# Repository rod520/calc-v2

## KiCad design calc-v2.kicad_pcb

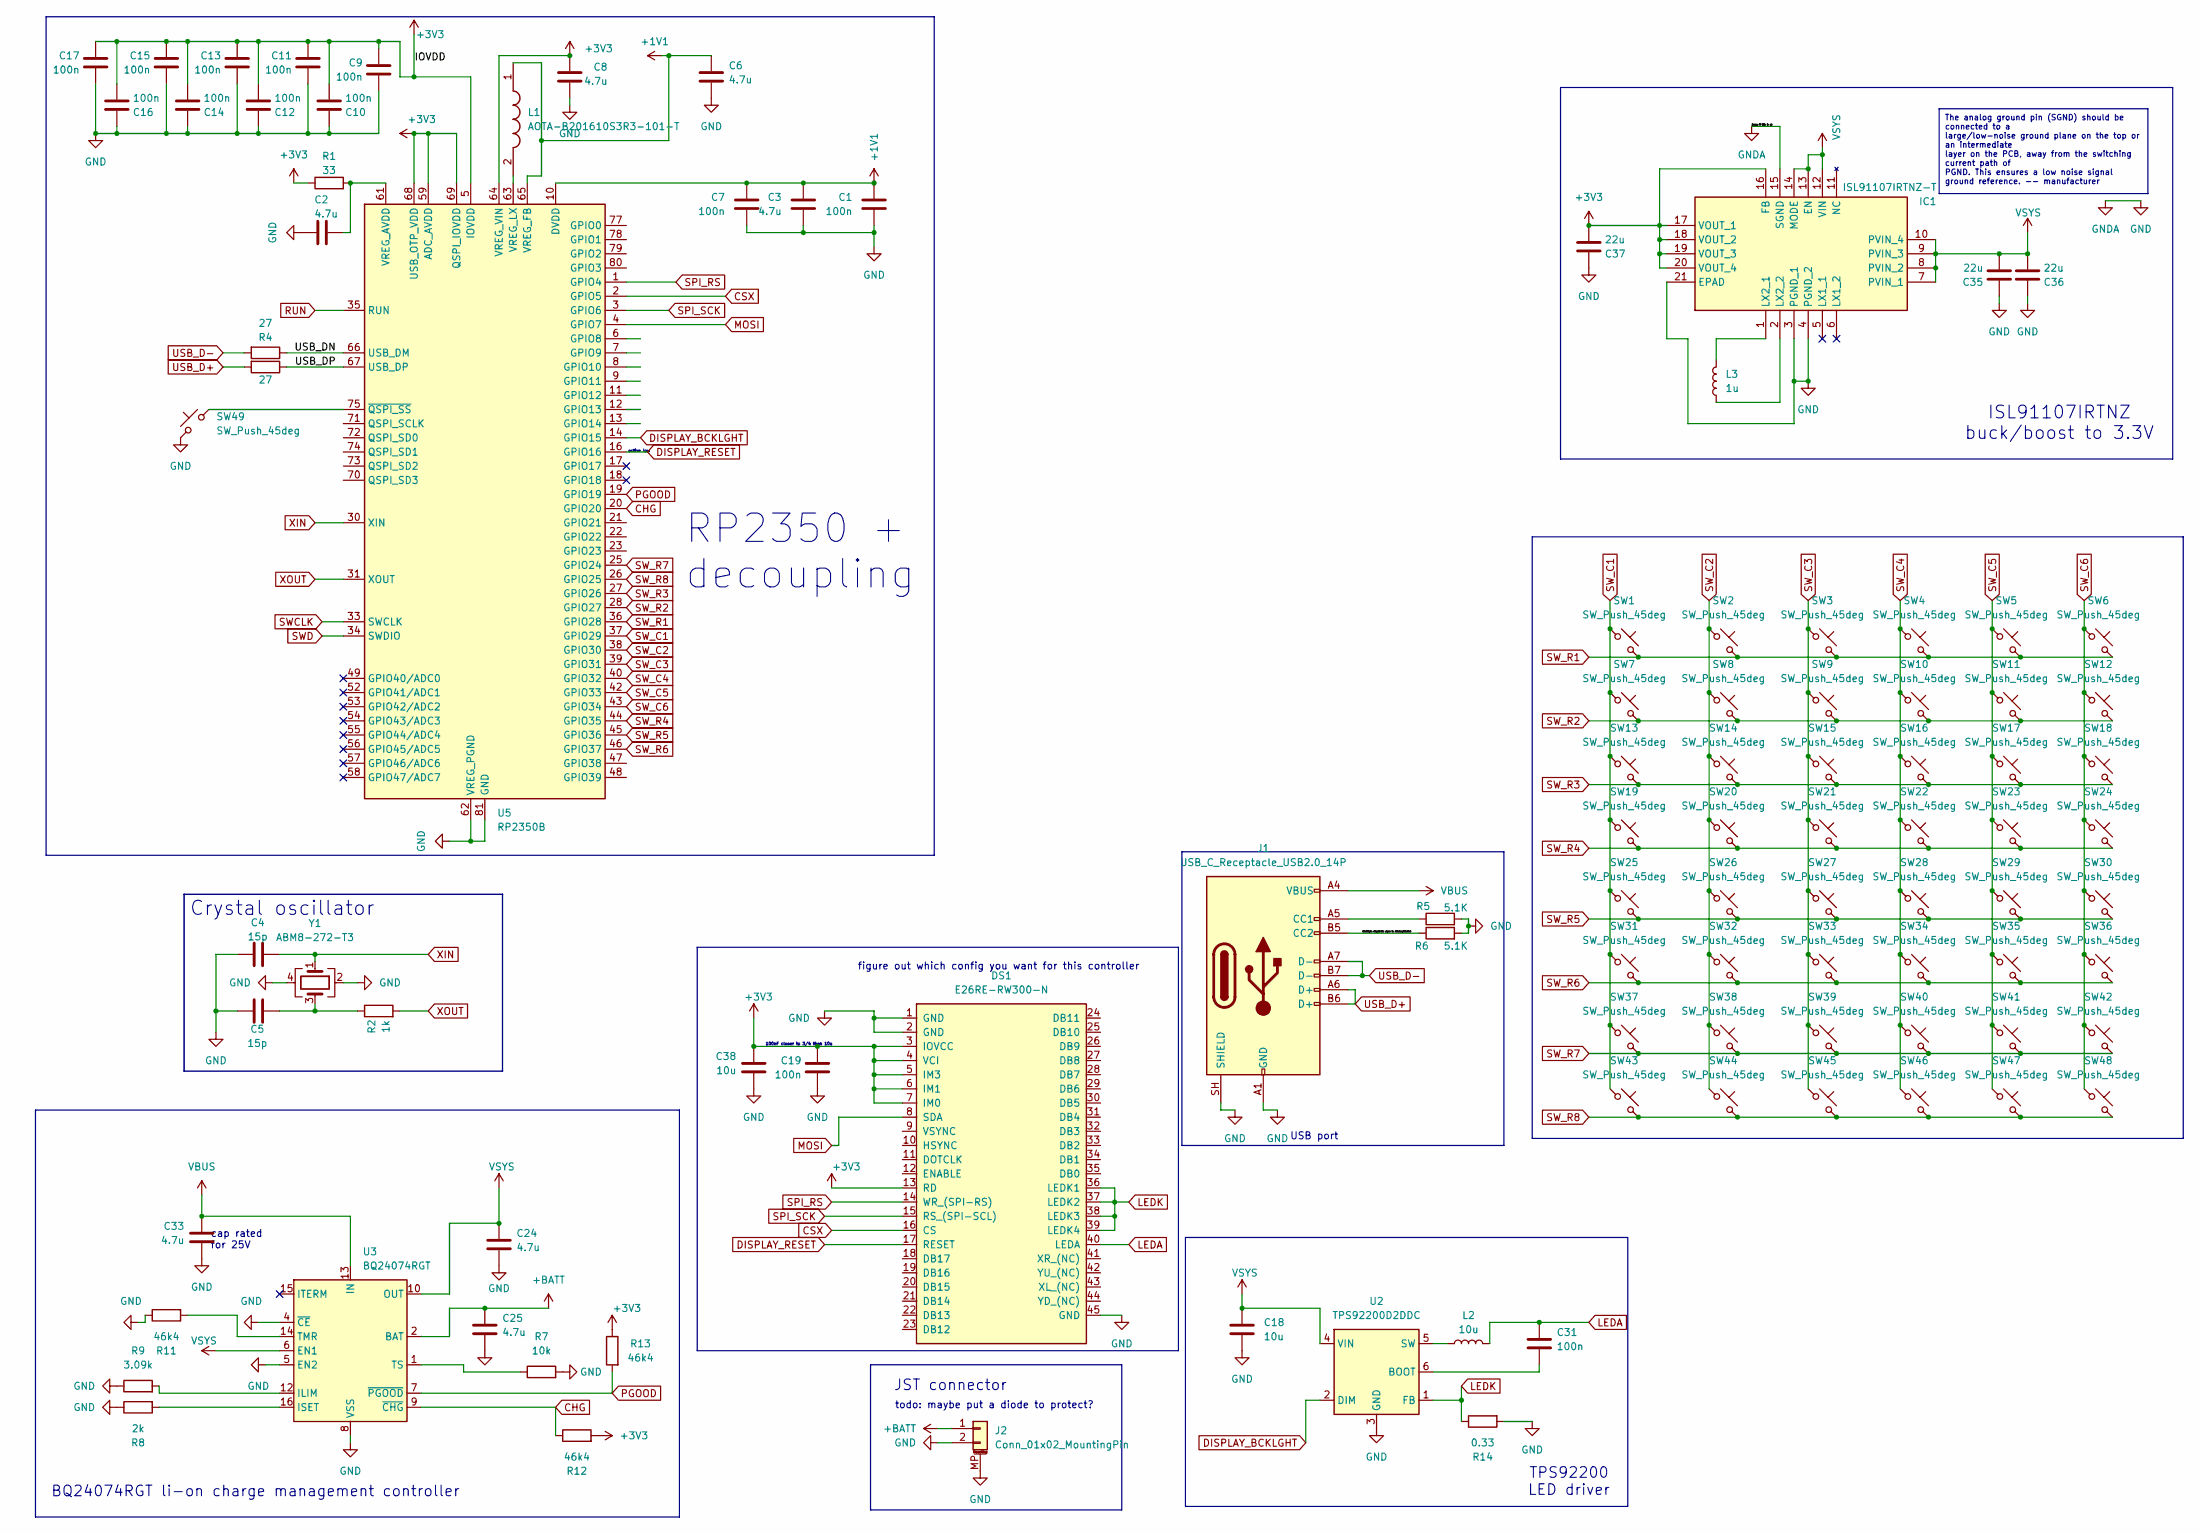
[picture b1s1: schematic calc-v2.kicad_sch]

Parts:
C1, C7, C9, C10, C11, C12, C13, C14, C15, C16, C17, C19, C31: 100n; C_0402_1005Metric
C2, C3, C6, C8, C24, C25, C33: 4.7u; C_0402_1005Metric
C4, C5: 15p; C_0402_1005Metric
C18, C38: 10u; C_0402_1005Metric
C35, C36, C37: 22u; C_0402_1005Metric
DS1: E26RE-RW300-N; HRS_FH12-45S-0.5SH_55_
IC1: ISL91107IRTNZ-T; QFN50P300X400X80-21N; Manufacturer_Part_Number ISL91107IRTNZ-T; Mouser Part Number 968-ISL91107IRTNZ-T
J1: USB_C_Receptacle_USB2.0_14P; USB_C_Receptacle_GCT_USB4105-xx-A_16P_TopMnt_Horizontal
J2: Conn_01x02_MountingPin; JST_PH_S2B-PH-SM4-TB_1x02-1MP_P2.00mm_Horizontal
L1: AOTA-B201610S3R3-101-T; AOTAB201610S3R3101T; Manufacturer_Part_Number AOTA-B201610S3R3-101-T; Mouser Part Number 815-AB201610S3R3101T
L2: 10u; L_0201_0603Metric
L3: 1u; L_0201_0603Metric
R1: 33; R_0201_0603Metric
R2: 1k; R_0402_1005Metric
R3, R4: 27; R_0201_0603Metric
R5, R6: 5.1K; R_0201_0603Metric
R7: 10k; R_0201_0603Metric
R8: 2k; R_0201_0603Metric
R9: 3.09k; R_0201_0603Metric
R11, R12, R13: 46k4; R_0201_0603Metric
R14: 0.33; R_0201_0603Metric
SW1, SW2, SW3, SW4, SW5, SW6, SW7, SW8, SW9, SW10, SW11, SW12, SW13, SW14, SW15, SW16, SW17, SW18, SW19, SW20, SW21, SW22, SW23, SW24, SW25, SW26, SW27, SW28, SW29, SW30, SW31, SW32, SW33, SW34, SW35, SW36, SW37, SW38, SW39, SW40, SW41, SW42, SW43, SW44, SW45, SW46, SW47, SW48, SW49: SW_Push_45deg; SW_TS04-66-43-BK-100-SMT
U2: TPS92200D2DDC; SOT-23-6
U3: BQ24074RGT; VQFN-16-1EP_3x3mm_P0.5mm_EP1.6x1.6mm
U5: RP2350B; QFN-80-1EP_10x10mm_P0.4mm_EP3.4x3.4mm
Y1: ABM8-272-T3; ABM8272T3

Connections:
+1V1: C1.1, C3.1, C6.1, C7.1, L1.1, U5.10 (DVDD), U5.32 (DVDD), U5.51 (DVDD), U5.65 (VREG_FB)
+3V3: C8.1, C9.1, C10.2, C11.1, C12.2, C13.1, C14.2, C15.1, C16.2, C17.1, C19.1, C37.2, C38.1, DS1.3 (IOVCC), DS1.4 (VCI), DS1.5 (IM3), DS1.6 (IM1), DS1.7 (IM0), DS1.13 (RD), IC1.16 (FB), IC1.17 (VOUT_1), IC1.18 (VOUT_2), IC1.19 (VOUT_3), IC1.20 (VOUT_4), R1.1, R12.2, R13.1, U5.5 (IOVDD), U5.15 (IOVDD), U5.24 (IOVDD), U5.29 (IOVDD), U5.41 (IOVDD), U5.50 (IOVDD), U5.59 (ADC_AVDD), U5.60 (IOVDD), U5.64 (VREG_VIN), U5.68 (USB_OTP_VDD), U5.69 (QSPI_IOVDD), U5.76 (IOVDD)
+BATT: C25.1, J2.1, U3.2 (BAT), U3.3 (BAT)
/Resistors should be close to microcontroller: J1.B5 (CC2), R6.1
/USB_DN: R4.1, U5.66 (USB_DM)
/USB_DP: R3.1, U5.67 (USB_DP)
CHG: R12.1, U3.9 (~CHG), U5.20 (GPIO20)
CSX: DS1.16 (CS), U5.2 (GPIO5)
DISPLAY_BCKLGHT: U2.2 (DIM), U5.14 (GPIO15)
DISPLAY_RESET: DS1.17 (RESET), U5.16 (GPIO16)
GND: C1.2, C2.2, C3.2, C4.1, C5.1, C6.2, C7.2, C8.2, C9.2, C10.1, C11.2, C12.1, C13.2, C14.1, C15.2, C16.1, C17.2, C18.2, C19.2, C24.2, C25.2, C33.2, C35.1, C36.1, C37.1, C38.2, DS1.1 (GND), DS1.2 (GND), DS1.45 (GND), IC1.3 (PGND_1), IC1.4 (PGND_2), IC1.15 (SGND), IC1.21 (EPAD), J1.A1 (GND), J1.A12 (GND), J1.B1 (GND), J1.B12 (GND), J1.SH (SHIELD), J2.2, J2.MP (MountPin), R5.2, R6.2, R7.2, R8.1, R9.1, R11.1, R14.2, SW49.1, U2.3 (GND), U3.4 (~CE), U3.5 (EN2), U3.8 (VSS), U3.17 (VSS), U5.62 (VREG_PGND), U5.81 (GND), Y1.2, Y1.4
LEDA: C31.1, DS1.40 (LEDA), L2.2
LEDK: DS1.36 (LEDK1), DS1.37 (LEDK2), DS1.38 (LEDK3), DS1.39 (LEDK4), R14.1, U2.1 (FB)
MOSI: DS1.8 (SDA), U5.4 (GPIO7)
unnamed: C5.2, R2.1, Y1.3
unnamed: IC1.1 (LX2_1), L3.2
unnamed: IC1.2 (LX2_2), L3.1
unnamed: J1.A5 (CC1), R5.1
unnamed: C31.2, U2.6 (BOOT)
unnamed: L2.1, U2.5 (SW)
unnamed: R9.2, U3.12 (ILIM)
unnamed: R8.2, U3.16 (ISET)
unnamed: R11.2, U3.14 (TMR)
unnamed: R7.1, U3.1 (TS)
unnamed: C2.1, R1.2, U5.61 (VREG_AVDD)
unnamed: L1.2, U5.63 (VREG_LX)
unnamed: SW49.2, U5.75 (~QSPI_SS)
PGOOD: R13.2, U3.7 (~PGOOD), U5.19 (GPIO19)
RUN: U5.35 (RUN)
SPI_RS: DS1.14 (WR_(SPI-RS)), U5.1 (GPIO4)
SPI_SCK: DS1.15 (RS_(SPI-SCL)), U5.3 (GPIO6)
SWCLK: U5.33 (SWCLK)
SWD: U5.34 (SWDIO)
SW_C1: SW1.1, SW7.1, SW13.1, SW19.1, SW25.1, SW31.1, SW37.1, SW43.1, U5.37 (GPIO29)
SW_C2: SW2.1, SW8.1, SW14.1, SW20.1, SW26.1, SW32.1, SW38.1, SW44.1, U5.38 (GPIO30)
SW_C3: SW3.1, SW9.1, SW15.1, SW21.1, SW27.1, SW33.1, SW39.1, SW45.1, U5.39 (GPIO31)
SW_C4: SW4.1, SW10.1, SW16.1, SW22.1, SW28.1, SW34.1, SW40.1, SW46.1, U5.40 (GPIO32)
SW_C5: SW5.1, SW11.1, SW17.1, SW23.1, SW29.1, SW35.1, SW41.1, SW47.1, U5.42 (GPIO33)
SW_C6: SW6.1, SW12.1, SW18.1, SW24.1, SW30.1, SW36.1, SW42.1, SW48.1, U5.43 (GPIO34)
SW_R1: SW1.2, SW2.2, SW3.2, SW4.2, SW5.2, SW6.2, U5.36 (GPIO28)
SW_R2: SW7.2, SW8.2, SW9.2, SW10.2, SW11.2, SW12.2, U5.28 (GPIO27)
SW_R3: SW13.2, SW14.2, SW15.2, SW16.2, SW17.2, SW18.2, U5.27 (GPIO26)
SW_R4: SW19.2, SW20.2, SW21.2, SW22.2, SW23.2, SW24.2, U5.44 (GPIO35)
SW_R5: SW25.2, SW26.2, SW27.2, SW28.2, SW29.2, SW30.2, U5.45 (GPIO36)
SW_R6: SW31.2, SW32.2, SW33.2, SW34.2, SW35.2, SW36.2, U5.46 (GPIO37)
SW_R7: SW37.2, SW38.2, SW39.2, SW40.2, SW41.2, SW42.2, U5.25 (GPIO24)
SW_R8: SW43.2, SW44.2, SW45.2, SW46.2, SW47.2, SW48.2, U5.26 (GPIO25)
USB_D+: J1.A6 (D+), J1.B6 (D+), R3.2
USB_D-: J1.A7 (D-), J1.B7 (D-), R4.2
VBUS: C33.1, J1.A4 (VBUS), J1.A9 (VBUS), J1.B4 (VBUS), J1.B9 (VBUS), U3.13 (IN)
VSYS: C18.1, C24.1, C35.2, C36.2, IC1.7 (PVIN_1), IC1.8 (PVIN_2), IC1.9 (PVIN_3), IC1.10 (PVIN_4), IC1.12 (VIN), IC1.13 (EN), IC1.14 (MODE), U2.4 (VIN), U3.6 (EN1), U3.10 (OUT), U3.11 (OUT)
XIN: C4.2, U5.30 (XIN), Y1.1
XOUT: R2.2, U5.31 (XOUT)

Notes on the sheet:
cap rated for 25V
active low
RP2350 + decoupling
100nF closer to 3/4 than 10u
TPS92200 LED driver
USB port
BQ24074RGT li-on charge management controller
ISL91107IRTNZ buck/boost to 3.3V
JST connector
todo: maybe put a diode to protect?
figure out which config you want for this controller
Crystal oscillator
The analog ground pin (SGND) should be connected to a large/low-noise ground plane on the top or an intermediate layer on the PCB, away from the switching current path of PGND. This ensures a low noise signal ground reference. -- manufacturer

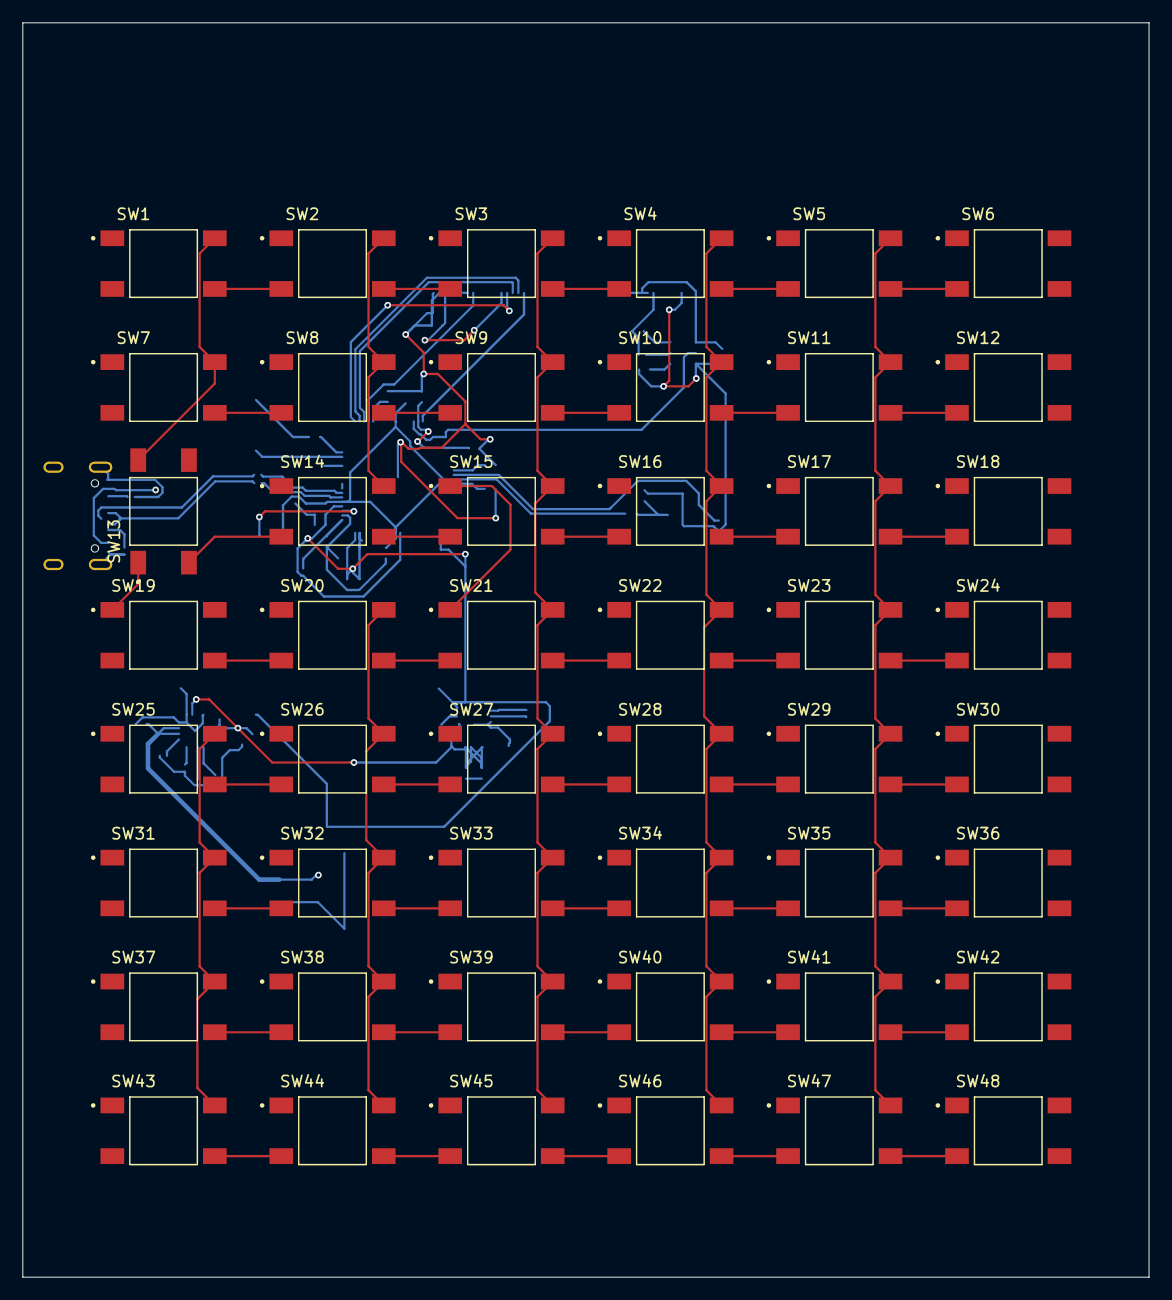
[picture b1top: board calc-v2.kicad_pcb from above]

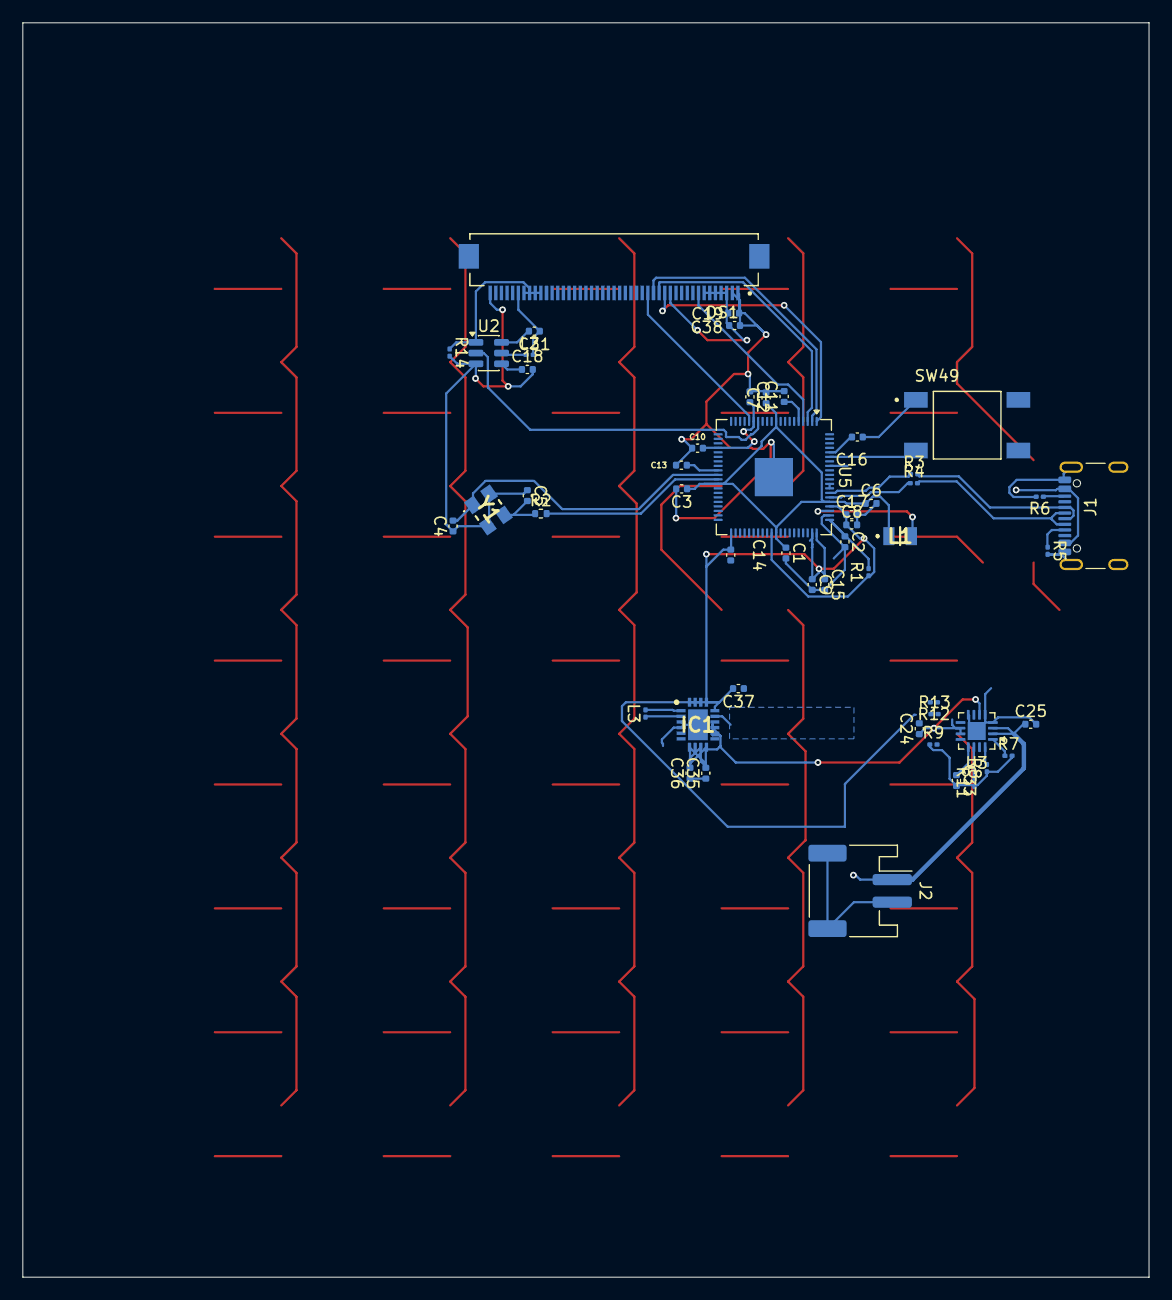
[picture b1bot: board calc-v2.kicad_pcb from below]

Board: 2 copper layers, 100.0 x 111.4 mm, 100 parts (52 on the bottom side), 50 nets.

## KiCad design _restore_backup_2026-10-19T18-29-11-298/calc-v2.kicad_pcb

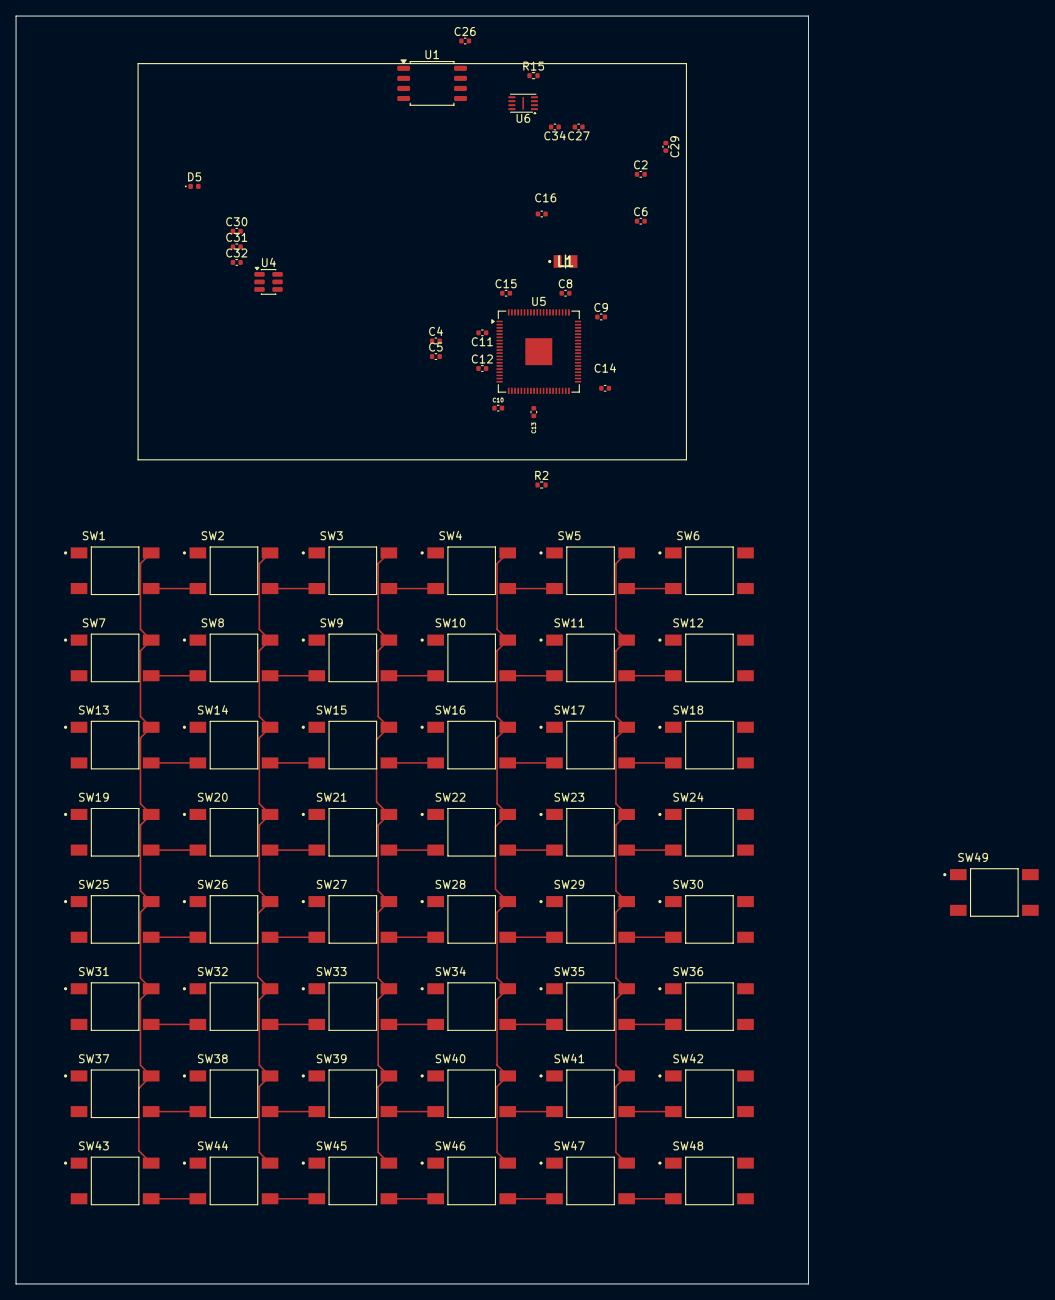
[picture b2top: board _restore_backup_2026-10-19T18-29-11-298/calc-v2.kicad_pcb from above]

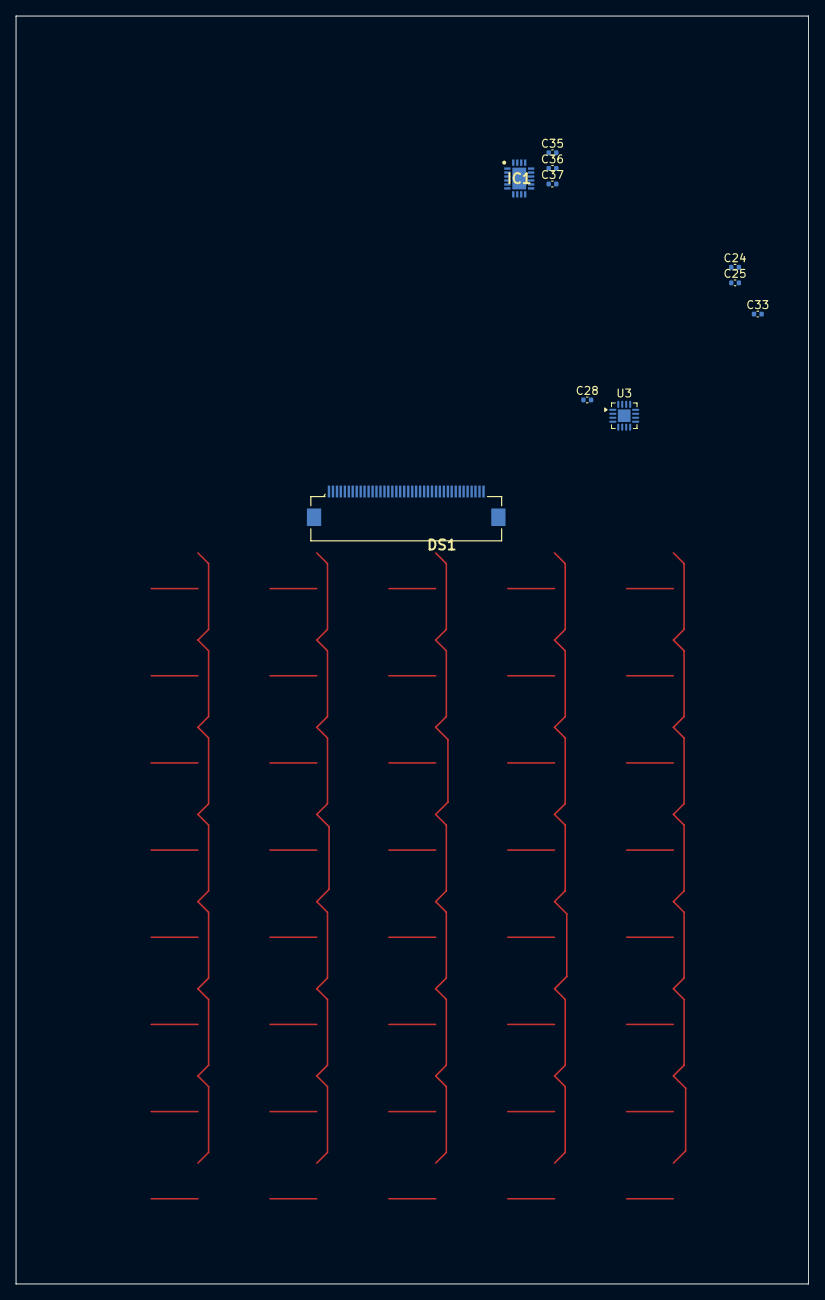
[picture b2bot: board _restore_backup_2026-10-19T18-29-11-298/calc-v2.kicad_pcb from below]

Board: 2 copper layers, 100.0 x 160.0 mm, 87 parts (10 on the bottom side), 50 nets.

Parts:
C2, C6, C8, C24, C25, C28, C29, C30, C33: 4.7u; C_0402_1005Metric
C4, C5: 15p; C_0402_1005Metric
C9, C10, C11, C12, C13, C14, C15, C16, C26, C27: 100n; C_0402_1005Metric
C31: 10u; C_0402_1005Metric
C32: 220n; C_0402_1005Metric
C34: 1u; C_0402_1005Metric
C35, C36, C37: 22u; C_0402_1005Metric
D5: D_Schottky; D_0402_1005Metric
DS1: E28GA-T-CW250-N; HIROSE_FH12S-40S-0.5SH_55_
IC1: ISL91107IRTNZ-T; QFN50P300X400X80-21N
L1: AOTA-B201610S3R3-101-T; AOTAB201610S3R3101T
R2, R15: 1k; R_0402_1005Metric
SW1, SW2, SW3, SW4, SW5, SW6, SW7, SW8, SW9, SW10, SW11, SW12, SW13, SW14, SW15, SW16, SW17, SW18, SW19, SW20, SW21, SW22, SW23, SW24, SW25, SW26, SW27, SW28, SW29, SW30, SW31, SW32, SW33, SW34, SW35, SW36, SW37, SW38, SW39, SW40, SW41, SW42, SW43, SW44, SW45, SW46, SW47, SW48, SW49: SW_Push_45deg; SW_TS04-66-43-BK-100-SMT
U1: W25Q128JVS; SOIC-8_5.3x5.3mm_P1.27mm
U3: BQ24074RGT; VQFN-16-1EP_3x3mm_P0.5mm_EP1.6x1.6mm
U4: TPS61165DBV; SOT-23-6
U5: RP2350B; QFN-80-1EP_10x10mm_P0.4mm_EP3.4x3.4mm
U6: APS6404L-3SQRx-ZR; Winbond_USON-8-1EP_3x2mm_P0.5mm_EP0.2x1.6mm

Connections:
+1V1: C6.1, L1.1, U5.10 (DVDD), U5.32 (DVDD), U5.51 (DVDD), U5.65 (VREG_FB)
+3V3: C8.1, C9.1, C10.2, C11.1, C12.2, C13.1, C14.2, C15.1, C16.2, C26.2, C27.2, C28.1, C29.2, C34.2, C37.2, DS1.8 (VDDI), DS1.9 (VDD), IC1.16 (FB), IC1.17 (VOUT_1), IC1.18 (VOUT_2), IC1.19 (VOUT_3), IC1.20 (VOUT_4), U1.8 (VCC), U5.5 (IOVDD), U5.15 (IOVDD), U5.24 (IOVDD), U5.29 (IOVDD), U5.41 (IOVDD), U5.50 (IOVDD), U5.59 (ADC_AVDD), U5.60 (IOVDD), U5.64 (VREG_VIN), U5.68 (USB_OTP_VDD), U5.69 (QSPI_IOVDD), U5.76 (IOVDD), U6.8 (VDD)
+BATT: C25.1, U3.2 (BAT), U3.3 (BAT)
CSX: DS1.10 (~CSX), U5.1 (GPIO4)
DB0: DS1.14 (DB0), U5.6 (GPIO8)
DB1: DS1.15 (DB1), U5.7 (GPIO9)
DB2: DS1.16 (DB2), U5.8 (GPIO10)
DB3: DS1.17 (DB3), U5.9 (GPIO11)
DB4: DS1.18 (DB4), U5.11 (GPIO12)
DB5: DS1.19 (DB5), U5.12 (GPIO13)
DB6: DS1.20 (DB6), U5.13 (GPIO14)
DB7: DS1.21 (DB7), U5.14 (GPIO15)
DCX: DS1.11 (DCX), U5.2 (GPIO5)
DISPLAY_RESET: DS1.38 (~RESX), U5.16 (GPIO16)
FLASH_IO0: U1.5 (DI/IO_{0}), U5.72 (QSPI_SD0), U6.5 (SI/SIO0)
FLASH_IO1: U1.2 (DO/IO_{1}), U5.74 (QSPI_SD1), U6.2 (SO/SIO1)
FLASH_IO2: U1.3 (~WP/IO_{2}), U5.73 (QSPI_SD2), U6.3 (SIO2)
FLASH_IO3: U1.7 (~HOLD/~RESET/IO_{3}), U5.70 (QSPI_SD3), U6.7 (SIO3)
FLASH_SCLK: U1.6 (CLK), U5.71 (QSPI_SCLK), U6.6 (SCLK)
FLASH_SS: R15.1, U1.1 (~CS), U5.75 (~QSPI_SS)
GND: C2.2, C4.1, C5.1, C6.2, C8.2, C9.2, C10.1, C11.2, C12.1, C13.2, C14.1, C15.2, C16.1, C24.2, C25.2, C26.1, C27.1, C28.2, C29.1, C30.2, C31.2, C32.1, C33.2, C34.1, C35.1, C36.1, C37.1, DS1.1 (GND), DS1.2 (GND), DS1.3 (IM0), DS1.4 (IM1), DS1.5 (IM2), DS1.6 (IM3), DS1.34 (DOTCLK), DS1.35 (ENABLE), IC1.3 (PGND_1), IC1.4 (PGND_2), IC1.15 (SGND), IC1.21 (EPAD), SW49.2, U1.4 (GND), U3.4 (~CE), U3.5 (EN2), U3.8 (VSS), U3.17 (VSS), U4.4 (GND), U5.62 (VREG_PGND), U5.81 (GND), U6.4 (VSS), U6.9 (EPAD)
LEDA: C31.1, D5.1 (K), DS1.40 (LEDA)
LEDK: DS1.39 (LEDK), U4.6 (FB)
unnamed: C5.2, R2.1
unnamed: D5.2 (A), U4.3 (SW)
unnamed: R15.2, SW49.1
unnamed: C32.2, U4.5 (COMP)
unnamed: C2.1, U5.61 (VREG_AVDD)
unnamed: L1.2, U5.63 (VREG_LX)
PSRAM_SS: U5.77 (GPIO0), U6.1 (~CE)
RDX: DS1.13 (~RDX), U5.4 (GPIO7)
SW_C1: SW1.1, SW7.1, SW13.1, SW19.1, SW25.1, SW31.1, SW37.1, SW43.1, U5.37 (GPIO29)
SW_C2: SW2.1, SW8.1, SW14.1, SW20.1, SW26.1, SW32.1, SW38.1, SW44.1, U5.38 (GPIO30)
SW_C3: SW3.1, SW9.1, SW15.1, SW21.1, SW27.1, SW33.1, SW39.1, SW45.1, U5.39 (GPIO31)
SW_C4: SW4.1, SW10.1, SW16.1, SW22.1, SW28.1, SW34.1, SW40.1, SW46.1, U5.40 (GPIO32)
SW_C5: SW5.1, SW11.1, SW17.1, SW23.1, SW29.1, SW35.1, SW41.1, SW47.1, U5.42 (GPIO33)
SW_C6: SW6.1, SW12.1, SW18.1, SW24.1, SW30.1, SW36.1, SW42.1, SW48.1, U5.43 (GPIO34)
SW_R1: SW1.2, SW2.2, SW3.2, SW4.2, SW5.2, SW6.2, U5.36 (GPIO28), U5.78 (GPIO1)
SW_R2: SW7.2, SW8.2, SW9.2, SW10.2, SW11.2, SW12.2, U5.28 (GPIO27), U5.79 (GPIO2)
SW_R3: SW13.2, SW14.2, SW15.2, SW16.2, SW17.2, SW18.2, U5.27 (GPIO26), U5.80 (GPIO3)
SW_R4: SW19.2, SW20.2, SW21.2, SW22.2, SW23.2, SW24.2, U5.21 (GPIO21)
SW_R5: SW25.2, SW26.2, SW27.2, SW28.2, SW29.2, SW30.2, U5.22 (GPIO22)
SW_R6: SW31.2, SW32.2, SW33.2, SW34.2, SW35.2, SW36.2, U5.23 (GPIO23)
SW_R7: SW37.2, SW38.2, SW39.2, SW40.2, SW41.2, SW42.2, U5.25 (GPIO24)
SW_R8: SW43.2, SW44.2, SW45.2, SW46.2, SW47.2, SW48.2, U5.26 (GPIO25)
VBUS: C33.1, U3.13 (IN)
VSYS: C24.1, C30.1, C35.2, C36.2, IC1.7 (PVIN_1), IC1.8 (PVIN_2), IC1.9 (PVIN_3), IC1.10 (PVIN_4), IC1.12 (VIN), IC1.13 (EN), IC1.14 (MODE), U3.6 (EN1), U3.10 (OUT), U3.11 (OUT), U4.1 (VIN)
WRX: DS1.12 (~WRX), U5.3 (GPIO6)
XIN: C4.2, U5.30 (XIN)
XOUT: R2.2, U5.31 (XOUT)
